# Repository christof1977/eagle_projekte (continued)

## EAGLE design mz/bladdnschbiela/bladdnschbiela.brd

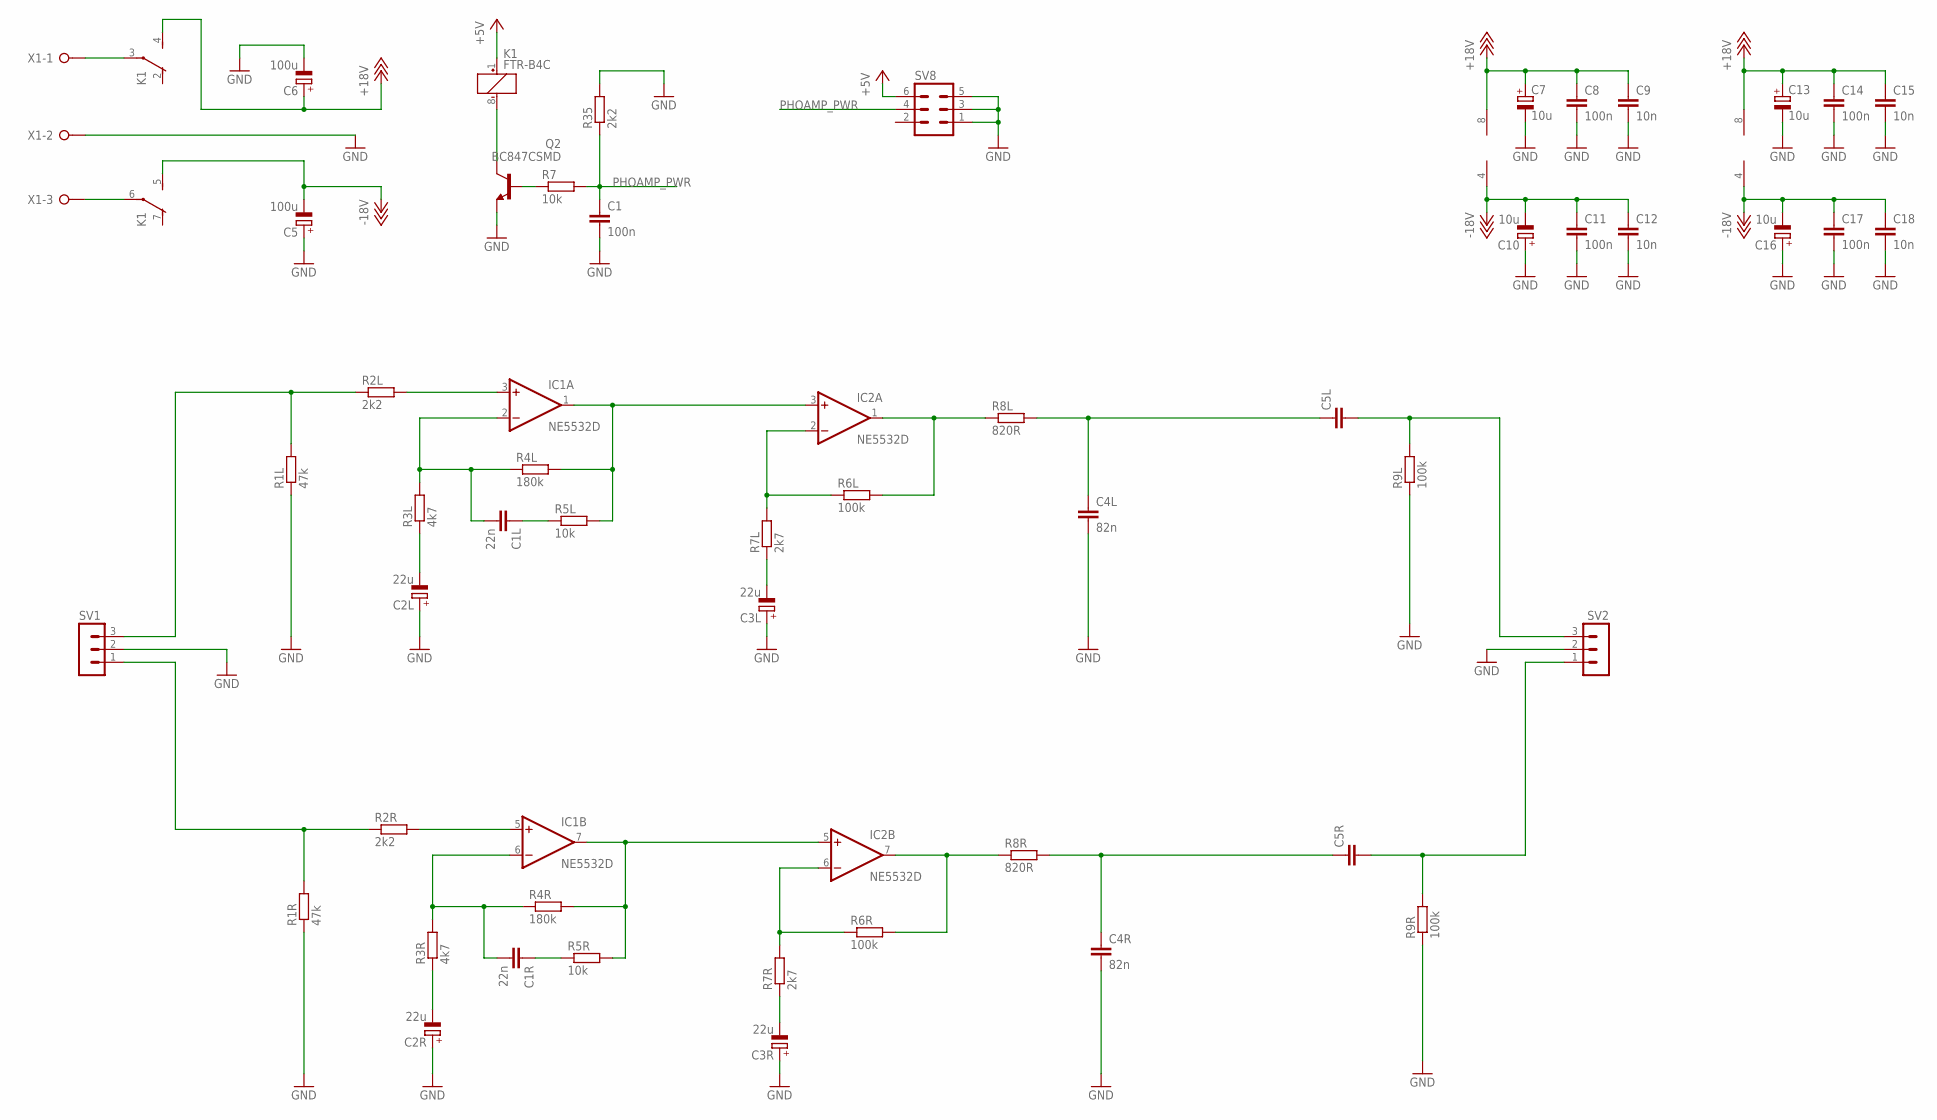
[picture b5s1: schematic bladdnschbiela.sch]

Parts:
C1: 100n; C0603
C1L, C1R: 22n; C1206
C2L, C2R, C3L, C3R: 22u; 153CLV-0405
C4L, C4R: 82n; C1210
C5, C6: 100u; 153CLV-0605
C5L, C5R: C5/7.2/11; C5B7.2_11
C7, C10, C13, C16: 10u; 153CLV-0405
C8, C11, C14, C17: 100n; C0805
C9, C12, C15, C18: 10n; C0805
IC1, IC2: NE5532D; SO08
K1: FTR-B4C
Q2: BC847CSMD; SOT23
R1L, R1R: 47k; R0603
R2L, R2R, R35: 2k2; R0603
R3L, R3R: 4k7; R0603
R4L, R4R: 180k; R0603
R5L, R5R, R7: 10k; R0603
R6L, R6R, R9L, R9R: 100k; R0603
R7L, R7R: 2k7; R0603
R8L, R8R: 820R; R0603
SV1, SV2: MA03-1
SV8: MA03-2B; MA03-2_BORDER
X1: W237-3E

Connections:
+5V: K1.1 (+), SV8.6
+18V: C6.+, C7.+, C8.1, C9.1, C13.+, C14.1, C15.1, IC1.8 (V+), IC2.8 (V+), K1.4 (S)
-18V: C5.-, C10.-, C11.1, C12.1, C16.-, C17.1, C18.1, IC1.4 (V-), IC2.4 (V-), K1.5 (S)
GND: C1.2, C2L.+, C2R.+, C3L.+, C3R.+, C4L.2, C4R.2, C5.+, C6.-, C7.-, C8.2, C9.2, C10.+, C11.2, C12.2, C13.-, C14.2, C15.2, C16.+, C17.2, C18.2, Q2.2 (E), R1L.1, R1R.1, R9L.1, R9R.1, R35.2, SV1.2, SV2.2, SV8.1, SV8.3, SV8.5, X1.2
unnamed: IC1.3 (+IN), R2L.2
unnamed: C1L.2, IC1.2 (-IN), R3L.2, R4L.1
unnamed: R1L.2, R2L.1, SV1.3
unnamed: C1L.1, R5L.1
unnamed: IC1.1 (OUT), IC2.3 (+IN), R4L.2, R5L.2
unnamed: IC2.2 (-IN), R6L.1, R7L.2
unnamed: C5L.2, R9L.2, SV2.3
unnamed: IC2.1 (OUT), R6L.2, R8L.1
unnamed: IC1.5 (+IN), R2R.2
unnamed: C4L.1, C5L.1, R8L.2
unnamed: C2L.-, R3L.1
unnamed: C3L.-, R7L.1
unnamed: C1R.2, IC1.6 (-IN), R3R.2, R4R.1
unnamed: R1R.2, R2R.1, SV1.1
unnamed: IC1.7 (OUT), IC2.5 (+IN), R4R.2, R5R.2
unnamed: IC2.6 (-IN), R6R.1, R7R.2
unnamed: IC2.7 (OUT), R6R.2, R8R.1
unnamed: C4R.1, C5R.1, R8R.2
unnamed: C2R.-, R3R.1
unnamed: C3R.-, R7R.1
unnamed: C1R.1, R5R.1
unnamed: C5R.2, R9R.2, SV2.1
unnamed: K1.3, X1.1
unnamed: Q2.1 (B), R7.1
unnamed: K1.6, X1.3
unnamed: K1.8 (-), Q2.3 (C)
PHOAMP_PWR: C1.1, R7.2, R35.1, SV8.4

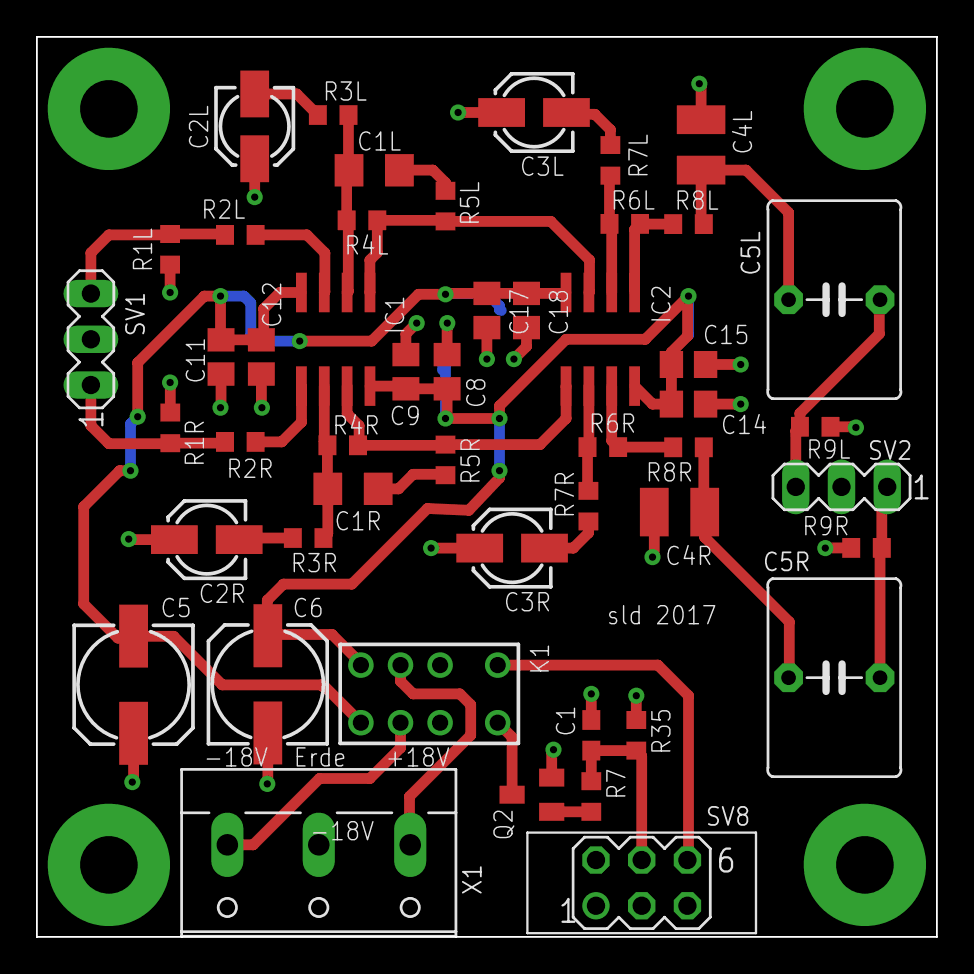
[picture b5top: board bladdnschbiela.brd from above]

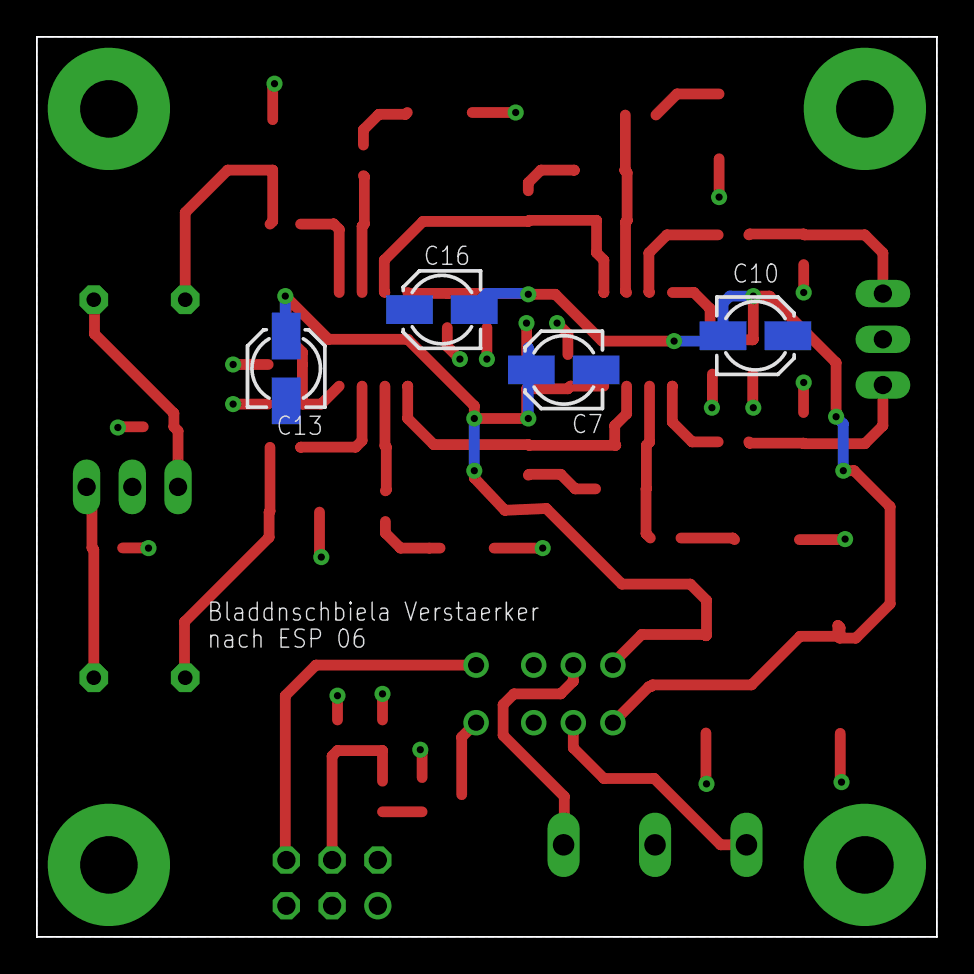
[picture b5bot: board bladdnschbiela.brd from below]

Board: 2 copper layers, 50.0 x 50.0 mm, 53 parts (4 on the bottom side), 31 nets.

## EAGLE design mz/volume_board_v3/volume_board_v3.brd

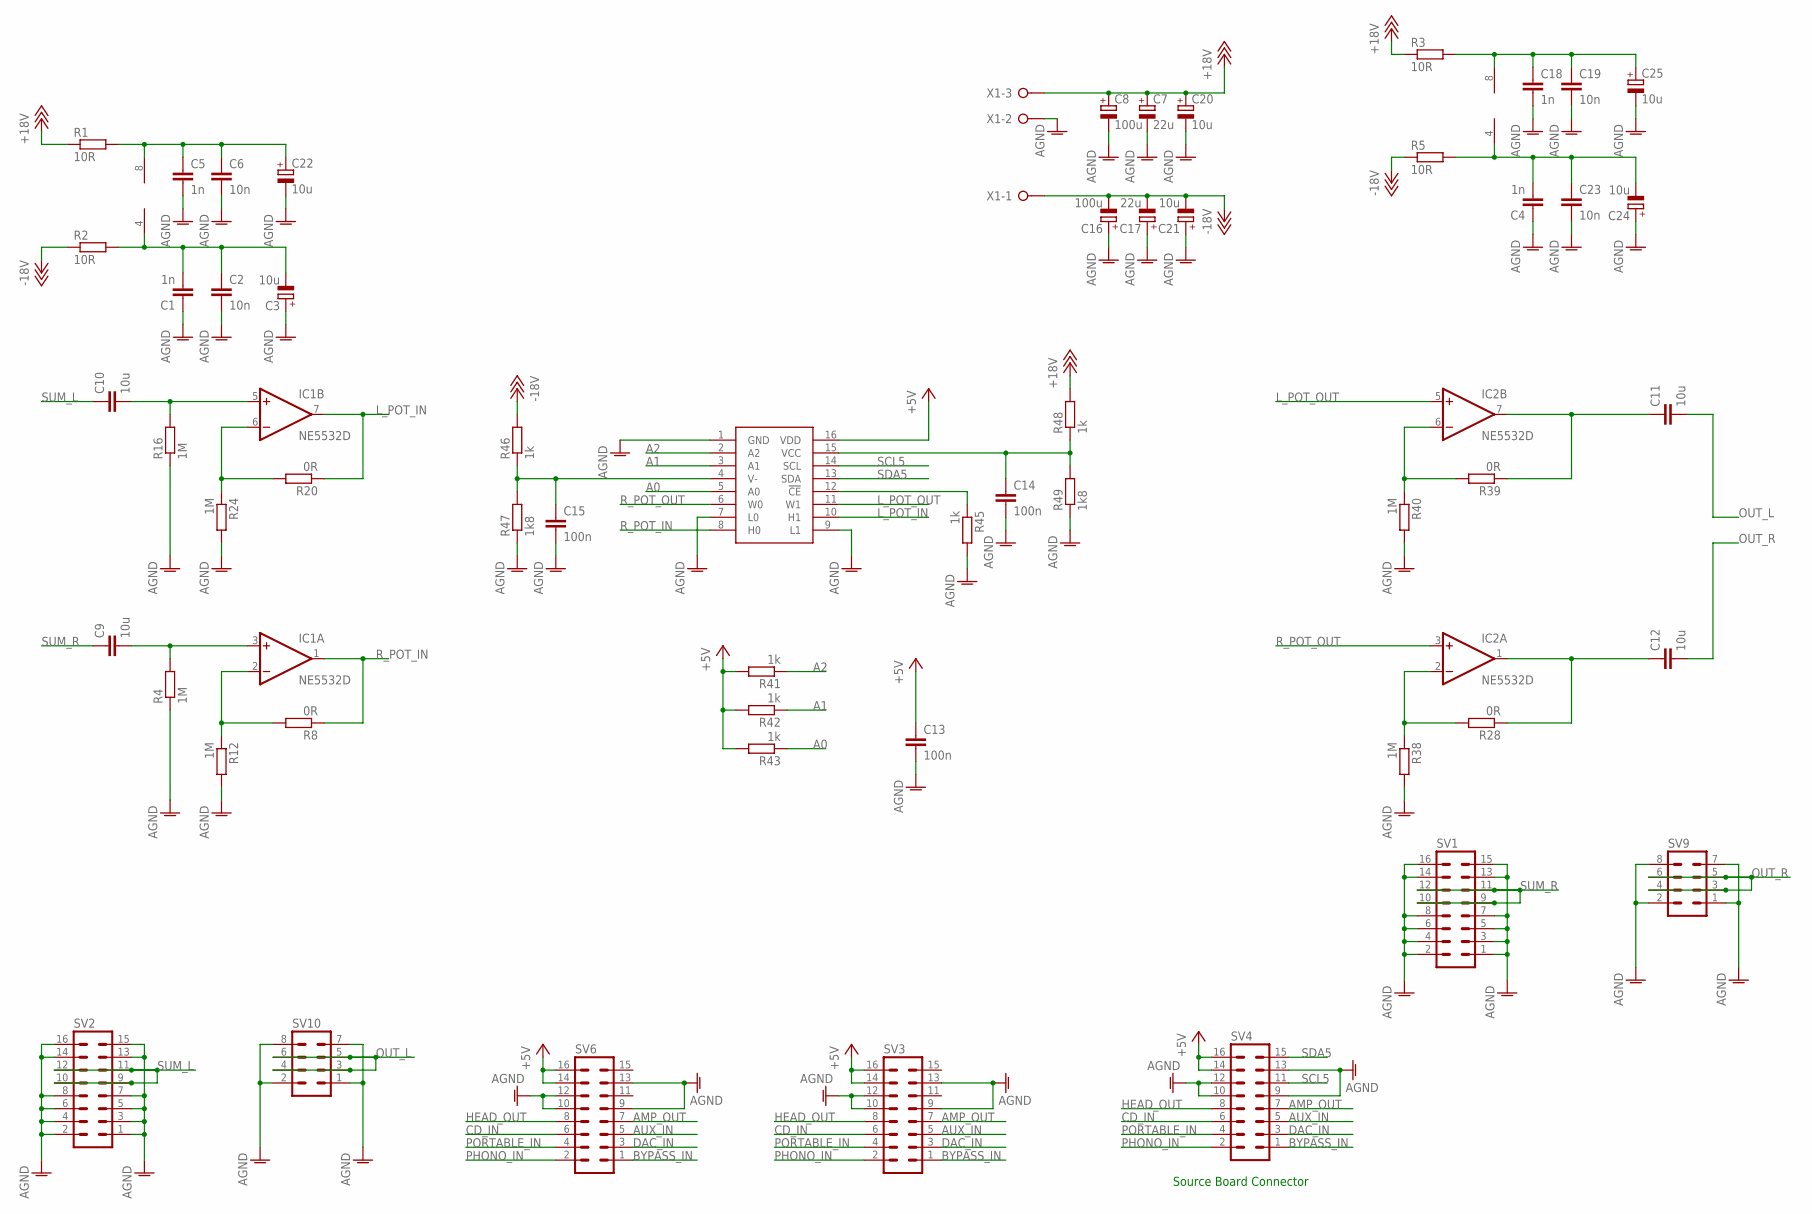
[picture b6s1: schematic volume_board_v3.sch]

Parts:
C1, C4, C5, C18: 1n; C0603
C2, C6, C19, C23: 10n; C0603
C3, C20, C21, C22, C24, C25: 10u; 153CLV-0405
C7, C17: 22u; 153CLV-0405
C8, C16: 100u; 153CLV-0605
C9, C10, C11, C12: 10u; C5B7.2_11
C13, C14, C15: 100n; C0603
IC1, IC2: NE5532D; SO08
IC4: DS1882; SO16
R1, R2, R3, R5: 10R; R0603
R4, R12, R16, R24, R38, R40: 1M; R0603
R8, R20, R28, R39: 0R; R0603
R41, R42, R43, R45, R46, R48: 1k; R0603
R47, R49: 1k8; R0603
SV1, SV2, SV3, SV6: MA08-2
SV4: MA08-2B; MA08-2_BORDER
SV9, SV10: MA04-2
X1: W237-3E

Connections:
+5V: C13.1, IC4.16 (VDD), R41.2, R42.2, R43.2, SV3.14, SV3.16, SV4.14, SV4.16, SV6.14, SV6.16
+18V: C7.+, C8.+, C20.+, R1.1, R3.1, R48.2, X1.3
-18V: C16.-, C17.-, C21.-, R2.1, R5.1, R46.2, X1.1
A0: IC4.5 (A0), R43.1
A1: IC4.3 (A1), R42.1
A2: IC4.2 (A2), R41.1
AMP_OUT: SV3.7, SV4.7, SV6.7
AUX_IN: SV3.5, SV4.5, SV6.5
BYPASS_IN: SV3.1, SV4.1, SV6.1
CD_IN: SV3.6, SV4.6, SV6.6
DAC_IN: SV3.3, SV4.3, SV6.3
GND: C1.1, C2.2, C3.+, C4.1, C5.2, C6.2, C7.-, C8.-, C13.2, C14.2, C15.2, C16.+, C17.+, C18.2, C19.2, C20.-, C21.+, C22.-, C23.2, C24.+, C25.-, IC4.1 (GND), IC4.7 (L0), IC4.9 (L1), R4.1, R12.2, R16.1, R24.2, R38.2, R40.2, R45.2, R47.1, R49.1, SV1.1, SV1.2, SV1.3, SV1.4, SV1.5, SV1.6, SV1.7, SV1.8, SV1.13, SV1.14, SV1.15, SV1.16, SV2.1, SV2.2, SV2.3, SV2.4, SV2.5, SV2.6, SV2.7, SV2.8, SV2.13, SV2.14, SV2.15, SV2.16, SV3.9, SV3.10, SV3.12, SV3.13, SV4.9, SV4.10, SV4.12, SV4.13, SV6.9, SV6.10, SV6.12, SV6.13, SV9.1, SV9.2, SV9.7, SV9.8, SV10.1, SV10.2, SV10.7, SV10.8, X1.2
HEAD_OUT: SV3.8, SV4.8, SV6.8
L_POT_IN: IC1.7 (OUT), IC4.10 (H1), R20.1
L_POT_OUT: IC2.5 (+IN), IC4.11 (W1)
unnamed: C1.2, C2.1, C3.-, IC1.4 (V-), R2.2
unnamed: C5.1, C6.1, C22.+, IC1.8 (V+), R1.2
unnamed: C18.1, C19.1, C25.+, IC2.8 (V+), R3.2
unnamed: C4.2, C23.1, C24.-, IC2.4 (V-), R5.2
unnamed: IC1.2 (-IN), R8.2, R12.1
unnamed: C9.2, IC1.3 (+IN), R4.2
unnamed: IC1.6 (-IN), R20.2, R24.1
unnamed: C10.2, IC1.5 (+IN), R16.2
unnamed: IC2.2 (-IN), R28.2, R38.1
unnamed: IC2.6 (-IN), R39.2, R40.1
unnamed: C11.1, IC2.7 (OUT), R39.1
unnamed: C12.1, IC2.1 (OUT), R28.1
unnamed: IC4.12 (!CE), R45.1
unnamed: C15.1, IC4.4 (V-), R46.1, R47.2
unnamed: C14.1, IC4.15 (VCC), R48.1, R49.2
OUT_L: C11.2, SV10.3, SV10.4, SV10.5, SV10.6
OUT_R: C12.2, SV9.3, SV9.4, SV9.5, SV9.6
PHONO_IN: SV3.2, SV4.2, SV6.2
PORTABLE_IN: SV3.4, SV4.4, SV6.4
R_POT_IN: IC1.1 (OUT), IC4.8 (H0), R8.1
R_POT_OUT: IC2.3 (+IN), IC4.6 (W0)
SCL5: IC4.14 (SCL), SV4.11
SDA5: IC4.13 (SDA), SV4.15
SUM_L: C10.1, SV2.9, SV2.10, SV2.11, SV2.12
SUM_R: C9.1, SV1.9, SV1.10, SV1.11, SV1.12

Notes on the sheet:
Source Board Connector

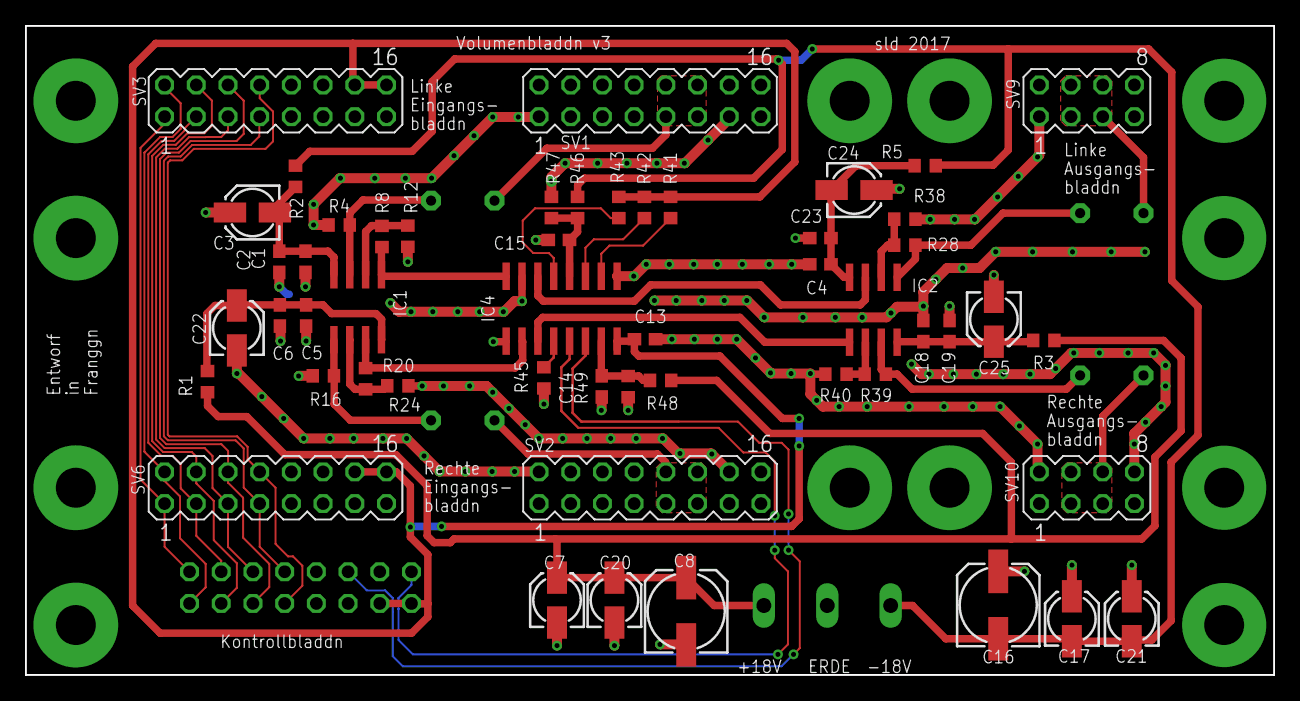
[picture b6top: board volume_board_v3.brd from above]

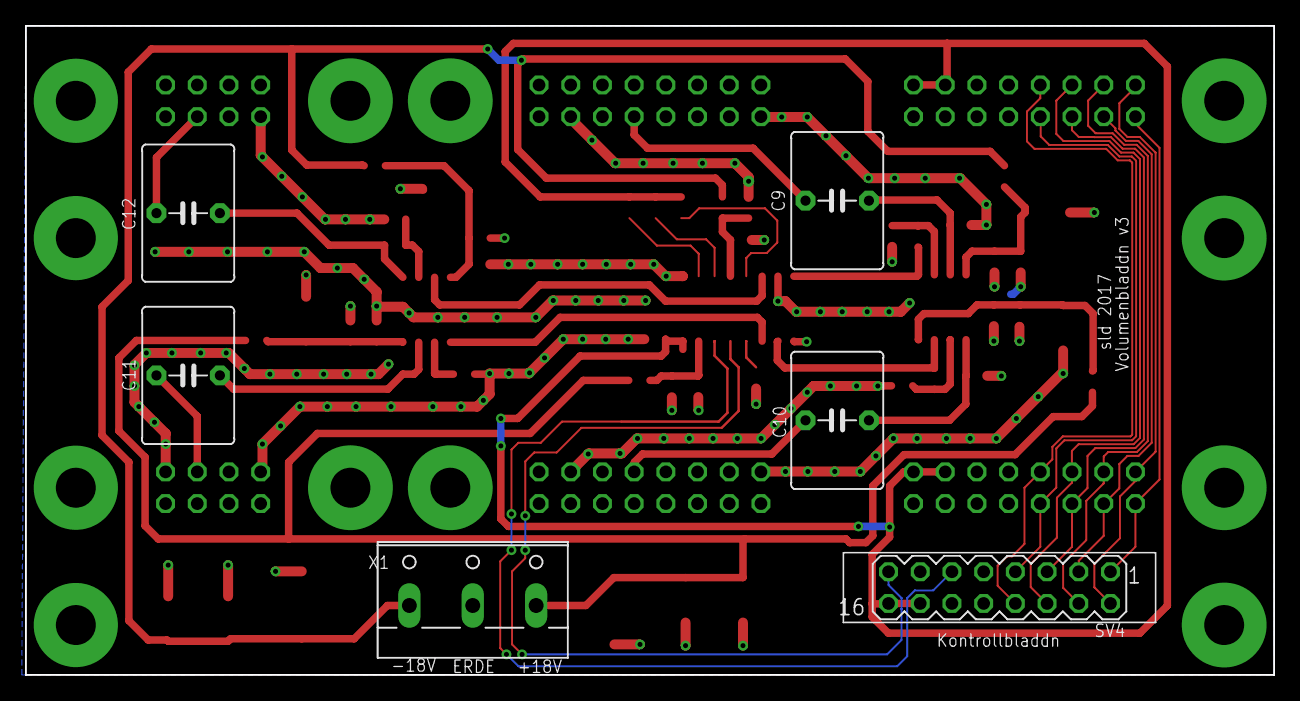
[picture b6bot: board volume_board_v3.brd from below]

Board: 2 copper layers, 100.0 x 52.0 mm, 58 parts (6 on the bottom side), 40 nets.

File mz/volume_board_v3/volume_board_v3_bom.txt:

Stückliste exportiert aus /Volumes/christof's home/eagle/mz/volume_board_v3/volume_board_v3.sch am 21.12.17 21:03

Part Value   Device             Package       Description                          MF MPN OC_FARNELL OC_NEWARK
C1   1n      C-EUC0603          C0603         CAPACITOR, European symbol                                      
C2   10n     C-EUC0603          C0603         CAPACITOR, European symbol                                      
C3   10u     CPOL-EU153CLV-0405 153CLV-0405   POLARIZED CAPACITOR, European symbol                            
C4   1n      C-EUC0603          C0603         CAPACITOR, European symbol                                      
C5   1n      C-EUC0603          C0603         CAPACITOR, European symbol                                      
C6   10n     C-EUC0603          C0603         CAPACITOR, European symbol                                      
C7   22u     CPOL-EU153CLV-0405 153CLV-0405   POLARIZED CAPACITOR, European symbol                            
C8   100u    CPOL-EU153CLV-0605 153CLV-0605   POLARIZED CAPACITOR, European symbol                            
C9   10u     C5/7.2/11          C5B7.2_11     CAPACITOR                                                       
C10  10u     C5/7.2/11          C5B7.2_11     CAPACITOR                                                       
C11  10u     C5/7.2/11          C5B7.2_11     CAPACITOR                                                       
C12  10u     C5/7.2/11          C5B7.2_11     CAPACITOR                                                       
C13  100n    C-EUC0603          C0603         CAPACITOR, European symbol                                      
C14  100n    C-EUC0603          C0603         CAPACITOR, European symbol                                      
C15  100n    C-EUC0603          C0603         CAPACITOR, European symbol                                      
C16  100u    CPOL-EU153CLV-0605 153CLV-0605   POLARIZED CAPACITOR, European symbol                            
C17  22u     CPOL-EU153CLV-0405 153CLV-0405   POLARIZED CAPACITOR, European symbol                            
C18  1n      C-EUC0603          C0603         CAPACITOR, European symbol                                      
C19  10n     C-EUC0603          C0603         CAPACITOR, European symbol                                      
C20  10u     CPOL-EU153CLV-0405 153CLV-0405   POLARIZED CAPACITOR, European symbol                            
C21  10u     CPOL-EU153CLV-0405 153CLV-0405   POLARIZED CAPACITOR, European symbol                            
C22  10u     CPOL-EU153CLV-0405 153CLV-0405   POLARIZED CAPACITOR, European symbol                            
C23  10n     C-EUC0603          C0603         CAPACITOR, European symbol                                      
C24  10u     CPOL-EU153CLV-0405 153CLV-0405   POLARIZED CAPACITOR, European symbol                            
C25  10u     CPOL-EU153CLV-0405 153CLV-0405   POLARIZED CAPACITOR, European symbol                            
IC1  NE5532D NE5532D            SO08          AUDIO AMPLIFIER                                                 
IC2  NE5532D NE5532D            SO08          AUDIO AMPLIFIER                                                 
IC4  DS1882  DS1882             SO16                                                                          
R1   10R     R-EU_R0603         R0603         RESISTOR, European symbol                                       
R2   10R     R-EU_R0603         R0603         RESISTOR, European symbol                                       
R3   10R     R-EU_R0603         R0603         RESISTOR, European symbol                                       
R4   1M      R-EU_R0603         R0603         RESISTOR, European symbol                                       
R5   10R     R-EU_R0603         R0603         RESISTOR, European symbol                                       
R8   0R      R-EU_R0603         R0603         RESISTOR, European symbol                                       
R12  1M      R-EU_R0603         R0603         RESISTOR, European symbol                                       
R16  1M      R-EU_R0603         R0603         RESISTOR, European symbol                                       
R20  0R      R-EU_R0603         R0603         RESISTOR, European symbol                                       
R24  1M      R-EU_R0603         R0603         RESISTOR, European symbol                                       
R28  0R      R-EU_R0603         R0603         RESISTOR, European symbol                                       
R38  1M      R-EU_R0603         R0603         RESISTOR, European symbol                                       
R39  0R      R-EU_R0603         R0603         RESISTOR, European symbol                                       
R40  1M      R-EU_R0603         R0603         RESISTOR, European symbol                                       
R41  1k      R-EU_R0603         R0603         RESISTOR, European symbol                                       
R42  1k      R-EU_R0603         R0603         RESISTOR, European symbol                                       
R43  1k      R-EU_R0603         R0603         RESISTOR, European symbol                                       
R45  1k      R-EU_R0603         R0603         RESISTOR, European symbol                                       
R46  1k      R-EU_R0603         R0603         RESISTOR, European symbol                                       
R47  1k8     R-EU_R0603         R0603         RESISTOR, European symbol                                       
R48  1k      R-EU_R0603         R0603         RESISTOR, European symbol                                       
R49  1k8     R-EU_R0603         R0603         RESISTOR, European symbol                                       
SV1          MA08-2             MA08-2        PIN HEADER                                  unknown    unknown  
SV2          MA08-2             MA08-2        PIN HEADER                                  unknown    unknown  
SV3          MA08-2             MA08-2        PIN HEADER                                  unknown    unknown  
SV4          MA08-2B            MA08-2_BORDER PIN HEADER                                                      
SV6          MA08-2             MA08-2        PIN HEADER                                  unknown    unknown  
SV9          MA04-2             MA04-2        PIN HEADER                                  unknown    unknown  
SV10         MA04-2             MA04-2        PIN HEADER                                  unknown    unknown  
X1           W237-3E            W237-3E       WAGO SREW CLAMP                             unknown    unknown

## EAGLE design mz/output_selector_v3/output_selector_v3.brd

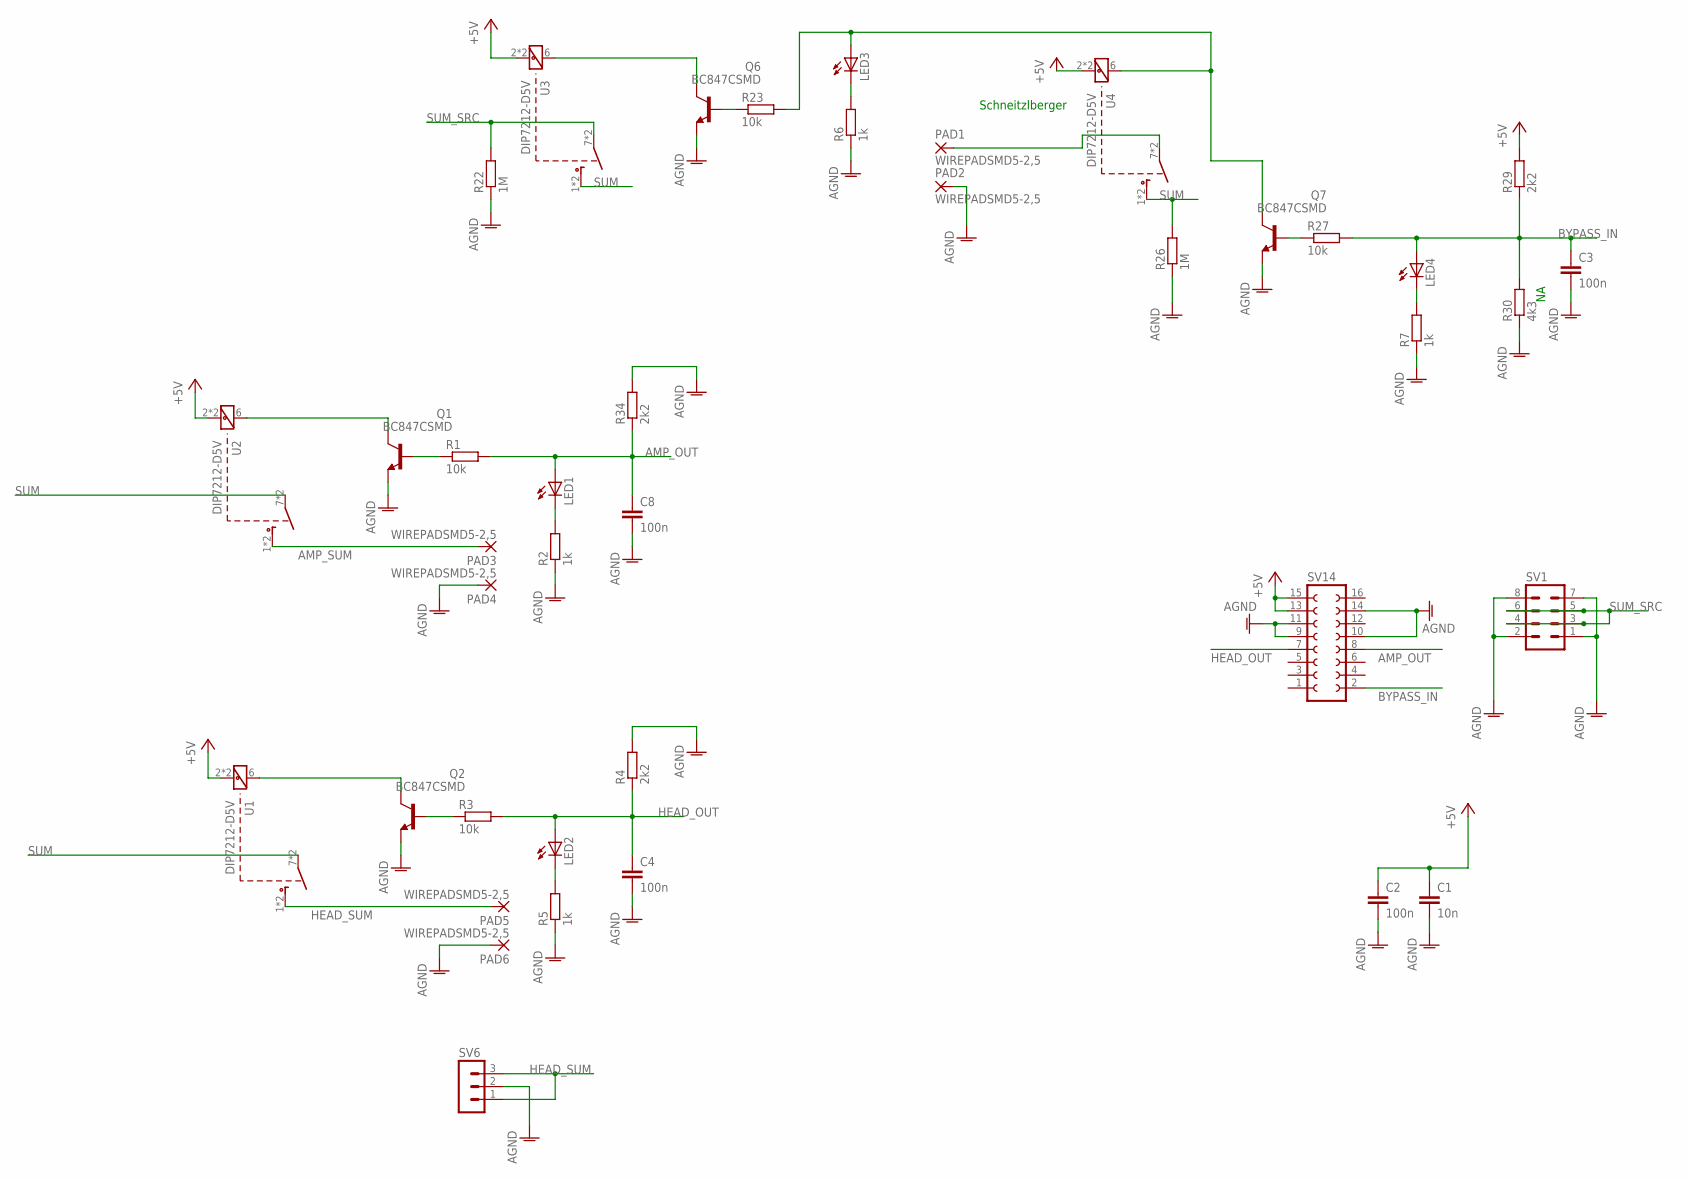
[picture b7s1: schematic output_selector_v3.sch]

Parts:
C1: 10n; C0603
C2, C3, C4, C8: 100n; C0603
LED1, LED2, LED3, LED4: LEDCHIPLED_0603; CHIPLED_0603
PAD1, PAD2, PAD3, PAD4, PAD5, PAD6: WIREPADSMD5-2,5; 5-2,5
Q1, Q2, Q6, Q7: BC847CSMD; SOT23
R1, R3, R23, R27: 10k; R0603
R2, R5, R6, R7: 1k; R0603
R4, R29, R34: 2k2; R0603
R22, R26: 1M; R0603
R30: 4k3; R0603
SV1: MA04-2W
SV6: MA03-1
SV14: FE08-2W
U1, U2, U3, U4: DIP7212-D5V; DP-07

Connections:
+5V: C1.1, C2.1, R29.2, SV14.13, SV14.15, U1.2 (1), U1.13 (1), U2.2 (1), U2.13 (1), U3.2 (1), U3.13 (1), U4.2 (1), U4.13 (1)
AGND: C1.2, C2.2, C3.2, C4.2, C8.2, PAD2.1, PAD4.1, PAD6.1, Q1.2 (E), Q2.2 (E), Q6.2 (E), Q7.2 (E), R2.1, R4.2, R5.1, R6.1, R7.1, R22.1, R26.1, R30.1, R34.2, SV1.1, SV1.2, SV1.7, SV1.8, SV6.2, SV14.9, SV14.10, SV14.11, SV14.14
AMP_OUT: C8.1, LED1.A, R1.2, R34.1, SV14.8
AMP_SUM: PAD3.1, U2.1 (6), U2.14 (6)
BYPASS_IN: C3.1, LED4.A, R27.2, R29.1, R30.2, SV14.2
HEAD_OUT: C4.1, LED2.A, R3.2, R4.1, SV14.7
HEAD_SUM: PAD5.1, SV6.1, SV6.3, U1.1 (6), U1.14 (6)
unnamed: LED3.A, Q7.3 (C), R23.2, U4.6 (2)
unnamed: Q1.3 (C), U2.6 (2)
unnamed: Q1.1 (B), R1.1
unnamed: Q2.3 (C), U1.6 (2)
unnamed: Q2.1 (B), R3.1
unnamed: LED1.C, R2.2
unnamed: LED2.C, R5.2
unnamed: LED3.C, R6.2
unnamed: LED4.C, R7.2
unnamed: Q6.1 (B), R23.1
unnamed: Q6.3 (C), U3.6 (2)
unnamed: PAD1.1, U4.7 (5), U4.8 (5)
unnamed: Q7.1 (B), R27.1
SUM: R26.2, U1.7 (5), U1.8 (5), U2.7 (5), U2.8 (5), U3.1 (6), U3.14 (6), U4.1 (6), U4.14 (6)
SUM_SRC: R22.2, SV1.3, SV1.4, SV1.5, SV1.6, U3.7 (5), U3.8 (5)

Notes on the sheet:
Schneitzlberger

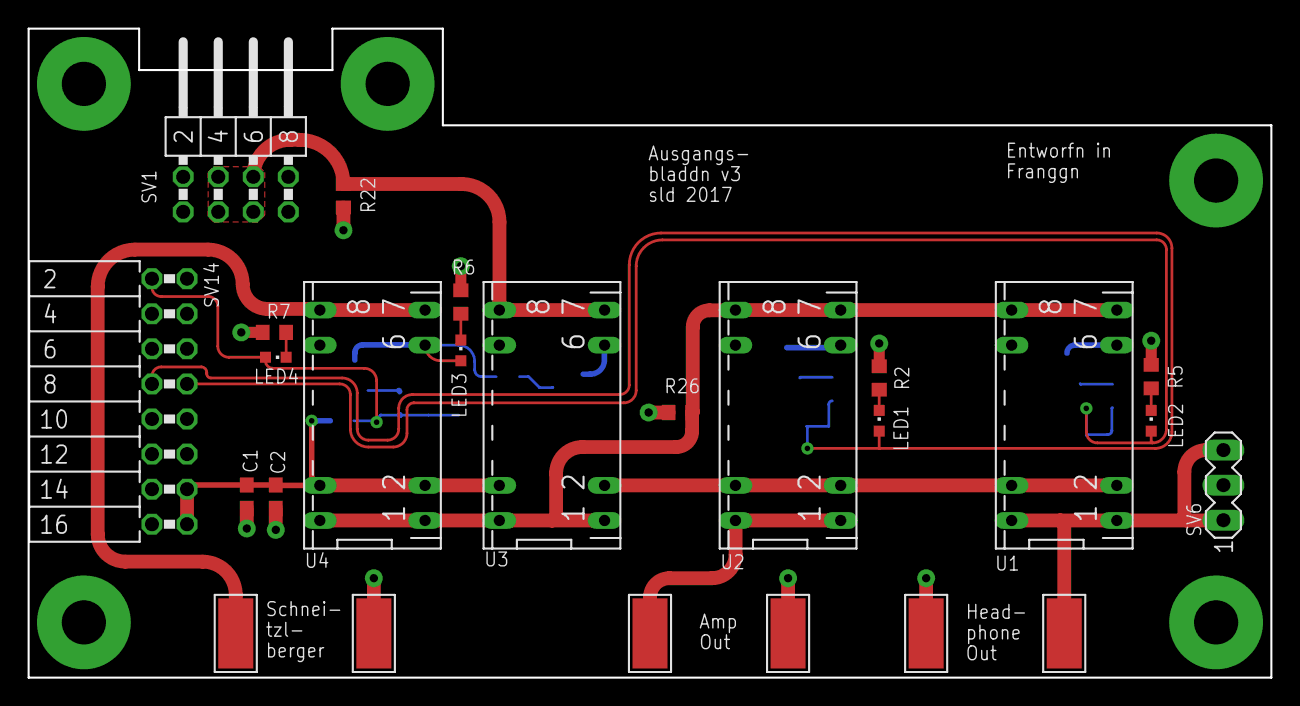
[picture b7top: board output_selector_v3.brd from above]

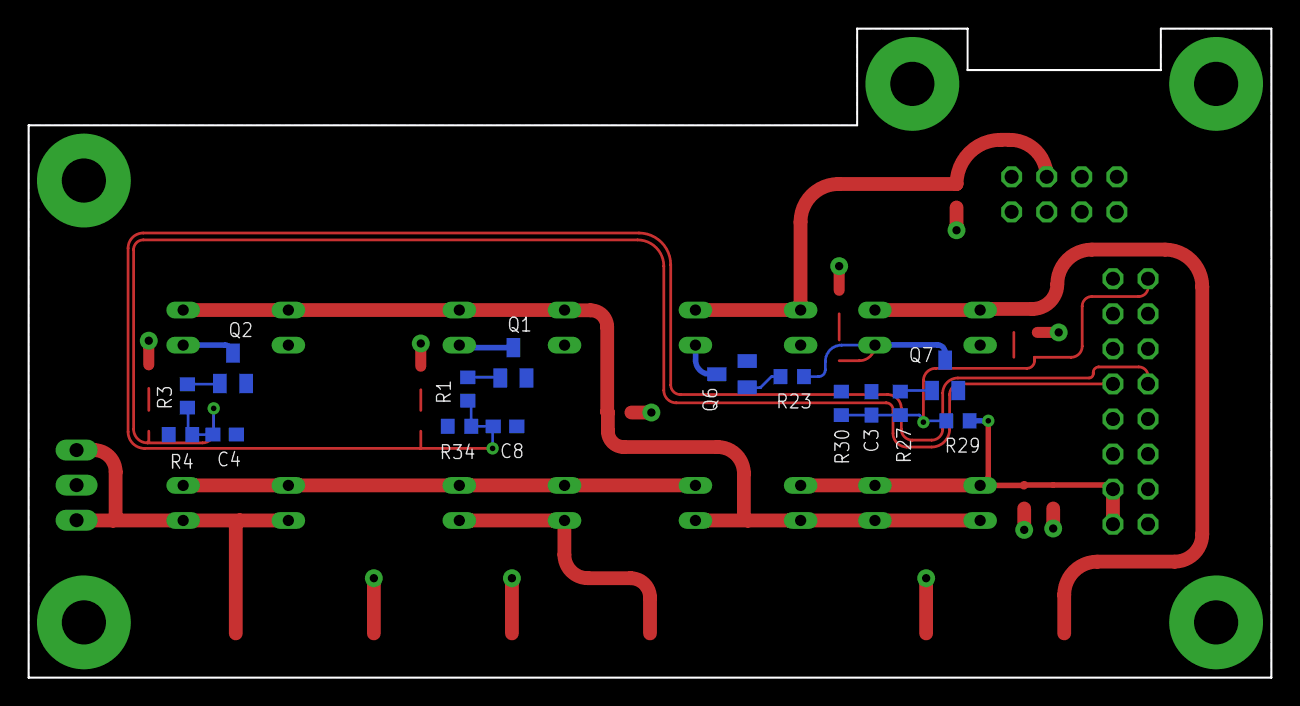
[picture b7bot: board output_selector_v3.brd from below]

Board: 2 copper layers, 90.0 x 47.0 mm, 40 parts (15 on the bottom side), 22 nets.

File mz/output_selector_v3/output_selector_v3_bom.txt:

Stückliste exportiert aus /Volumes/christof's home/eagle/mz/output_selector_v3/output_selector_v3.sch am 21.12.17 21:01

Part Value           Device          Package      Description                  MF MPN OC_FARNELL OC_NEWARK
C1   10n             C-EUC0603       C0603        CAPACITOR, European symbol                              
C2   100n            C-EUC0603       C0603        CAPACITOR, European symbol                              
C3   100n            C-EUC0603       C0603        CAPACITOR, European symbol                              
C4   100n            C-EUC0603       C0603        CAPACITOR, European symbol                              
C8   100n            C-EUC0603       C0603        CAPACITOR, European symbol                              
LED1                 LEDCHIPLED_0603 CHIPLED_0603 LED                                                     
LED2                 LEDCHIPLED_0603 CHIPLED_0603 LED                                                     
LED3                 LEDCHIPLED_0603 CHIPLED_0603 LED                                                     
LED4                 LEDCHIPLED_0603 CHIPLED_0603 LED                                                     
PAD1 WIREPADSMD5-2,5 WIREPADSMD5-2,5 5-2,5        Wire PAD connect wire on PCB                            
PAD2 WIREPADSMD5-2,5 WIREPADSMD5-2,5 5-2,5        Wire PAD connect wire on PCB                            
PAD3 WIREPADSMD5-2,5 WIREPADSMD5-2,5 5-2,5        Wire PAD connect wire on PCB                            
PAD4 WIREPADSMD5-2,5 WIREPADSMD5-2,5 5-2,5        Wire PAD connect wire on PCB                            
PAD5 WIREPADSMD5-2,5 WIREPADSMD5-2,5 5-2,5        Wire PAD connect wire on PCB                            
PAD6 WIREPADSMD5-2,5 WIREPADSMD5-2,5 5-2,5        Wire PAD connect wire on PCB                            
Q1   BC847CSMD       BC847CSMD       SOT23        NPN Transistor                                          
Q2   BC847CSMD       BC847CSMD       SOT23        NPN Transistor                                          
Q6   BC847CSMD       BC847CSMD       SOT23        NPN Transistor                                          
Q7   BC847CSMD       BC847CSMD       SOT23        NPN Transistor                                          
R1   10k             R-EU_R0603      R0603        RESISTOR, European symbol                               
R2   1k              R-EU_R0603      R0603        RESISTOR, European symbol                               
R3   10k             R-EU_R0603      R0603        RESISTOR, European symbol                               
R4   2k2             R-EU_R0603      R0603        RESISTOR, European symbol                               
R5   1k              R-EU_R0603      R0603        RESISTOR, European symbol                               
R6   1k              R-EU_R0603      R0603        RESISTOR, European symbol                               
R7   1k              R-EU_R0603      R0603        RESISTOR, European symbol                               
R22  1M              R-EU_R0603      R0603        RESISTOR, European symbol                               
R23  10k             R-EU_R0603      R0603        RESISTOR, European symbol                               
R26  1M              R-EU_R0603      R0603        RESISTOR, European symbol                               
R27  10k             R-EU_R0603      R0603        RESISTOR, European symbol                               
R29  2k2             R-EU_R0603      R0603        RESISTOR, European symbol                               
R30  4k3             R-EU_R0603      R0603        RESISTOR, European symbol                               
R34  2k2             R-EU_R0603      R0603        RESISTOR, European symbol                               
SV1                  MA04-2W         MA04-2W                                                              
SV6                  MA03-1          MA03-1       PIN HEADER                          unknown    unknown  
SV14                 FE08-2W         FE08-2W      FEMALE HEADER                       unknown    unknown  
U1   DIP7212-D5V     DIP7212-D5V     DP-07        Meder DIP 7212-D 5V                                     
U2   DIP7212-D5V     DIP7212-D5V     DP-07        Meder DIP 7212-D 5V                                     
U3   DIP7212-D5V     DIP7212-D5V     DP-07        Meder DIP 7212-D 5V                                     
U4   DIP7212-D5V     DIP7212-D5V     DP-07        Meder DIP 7212-D 5V
